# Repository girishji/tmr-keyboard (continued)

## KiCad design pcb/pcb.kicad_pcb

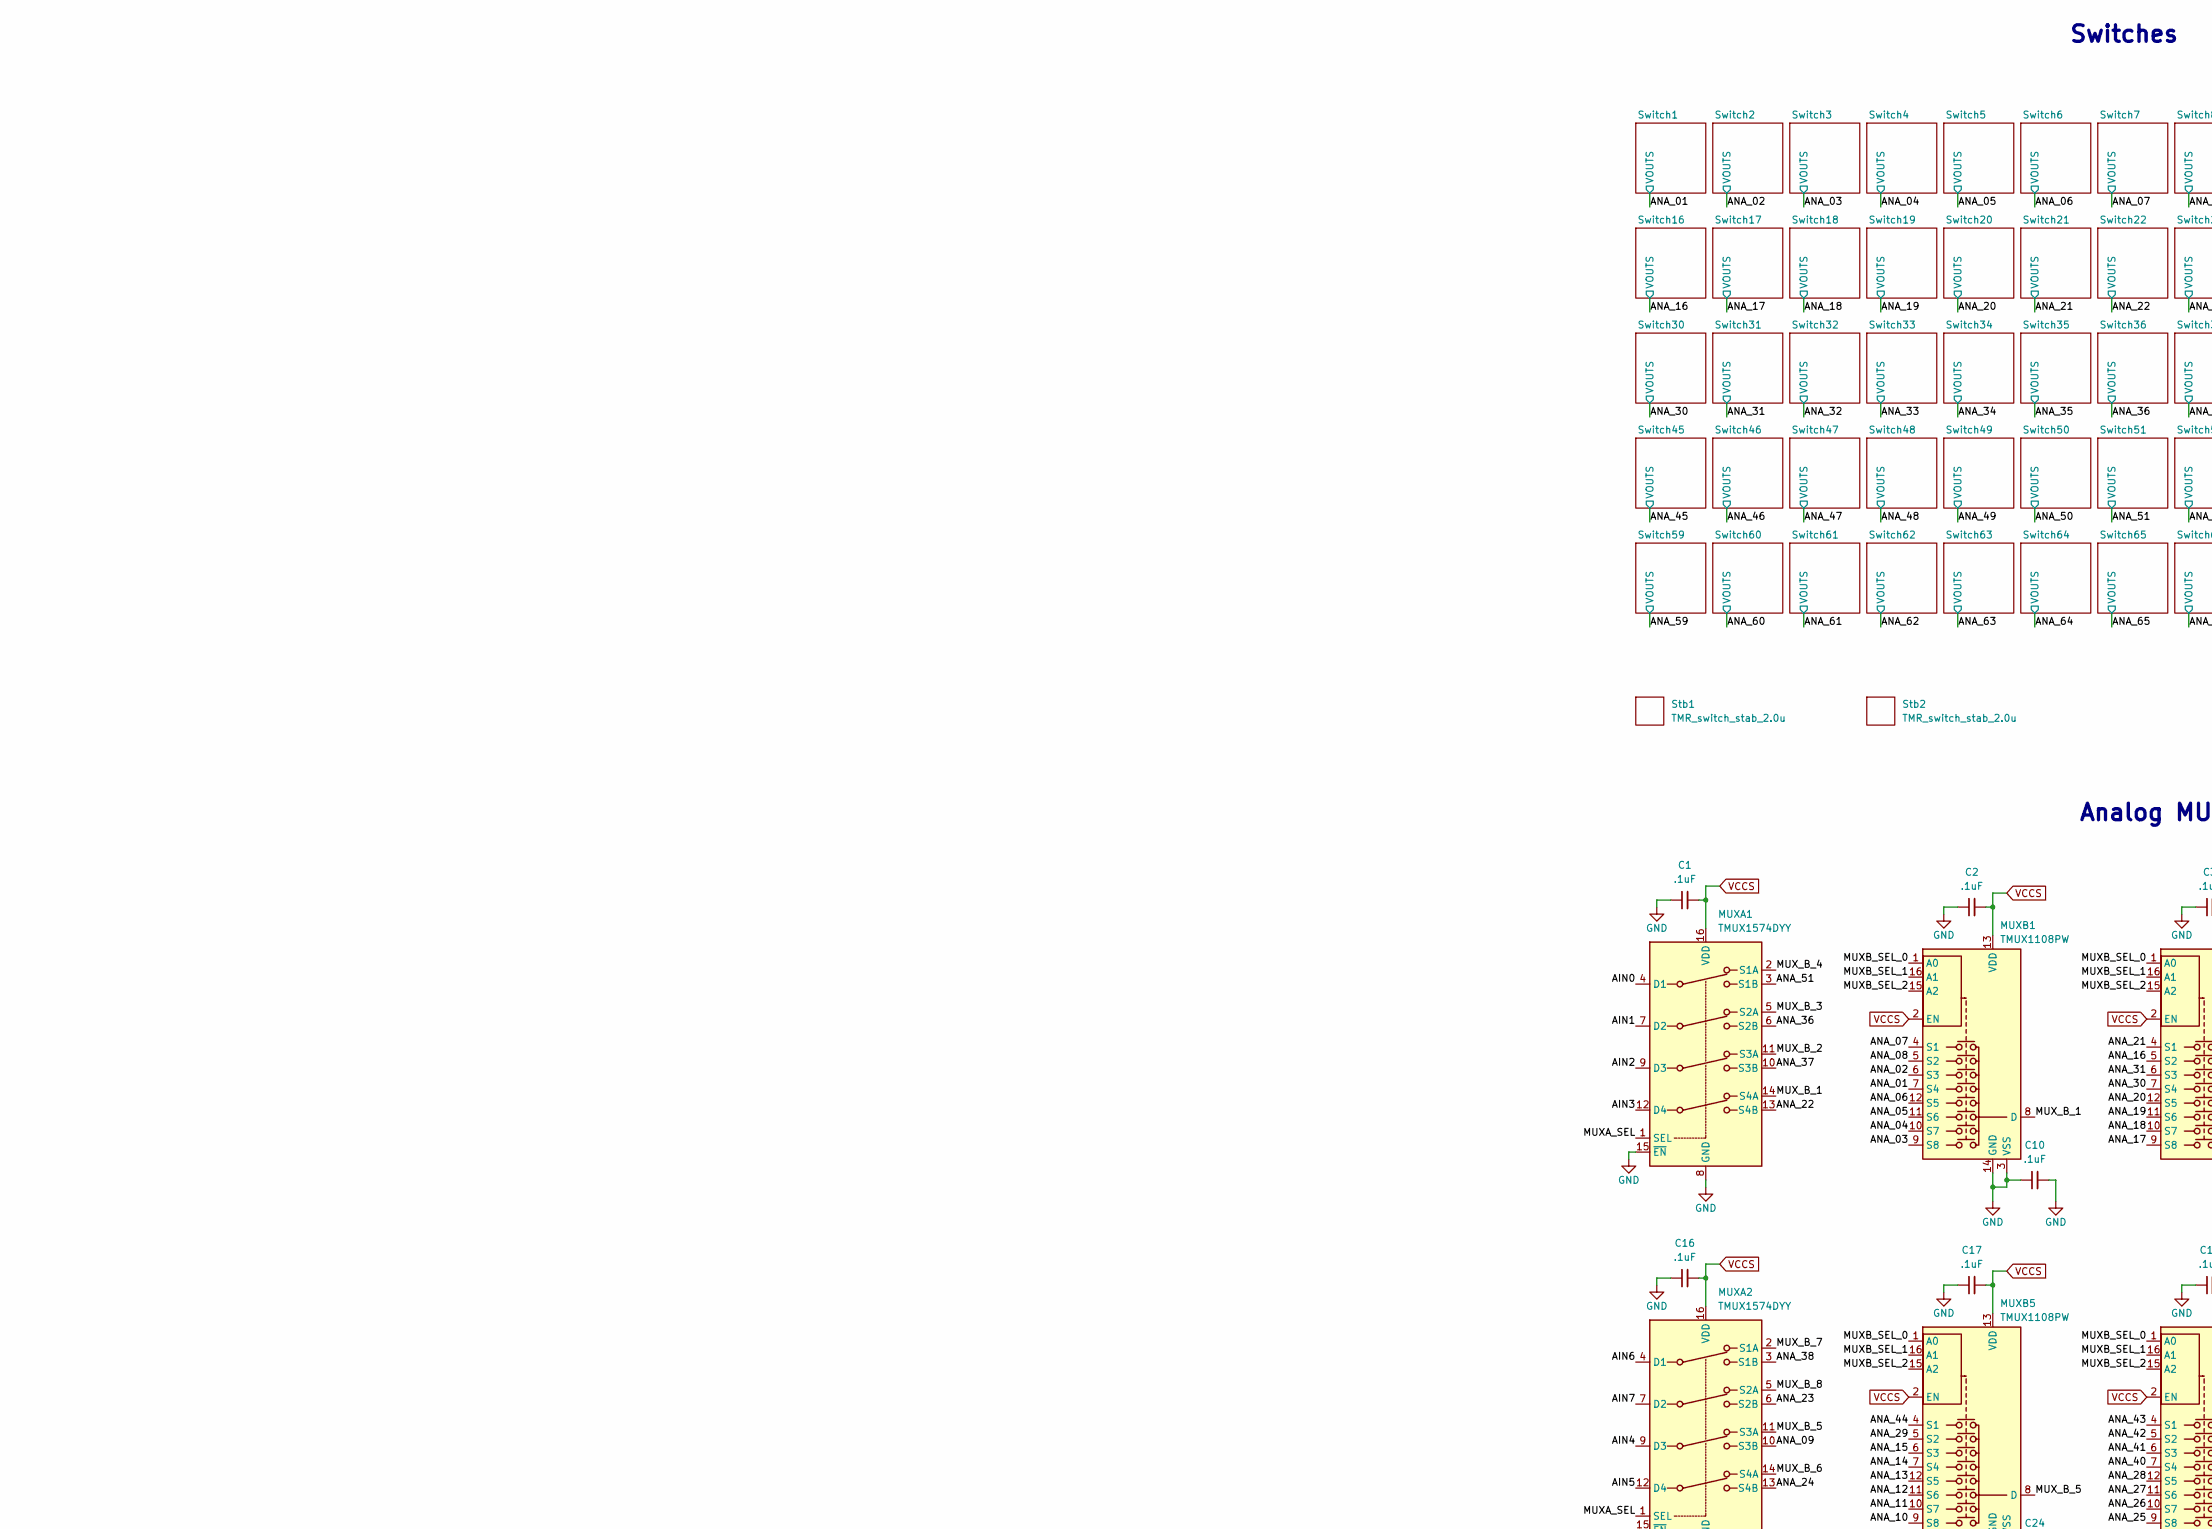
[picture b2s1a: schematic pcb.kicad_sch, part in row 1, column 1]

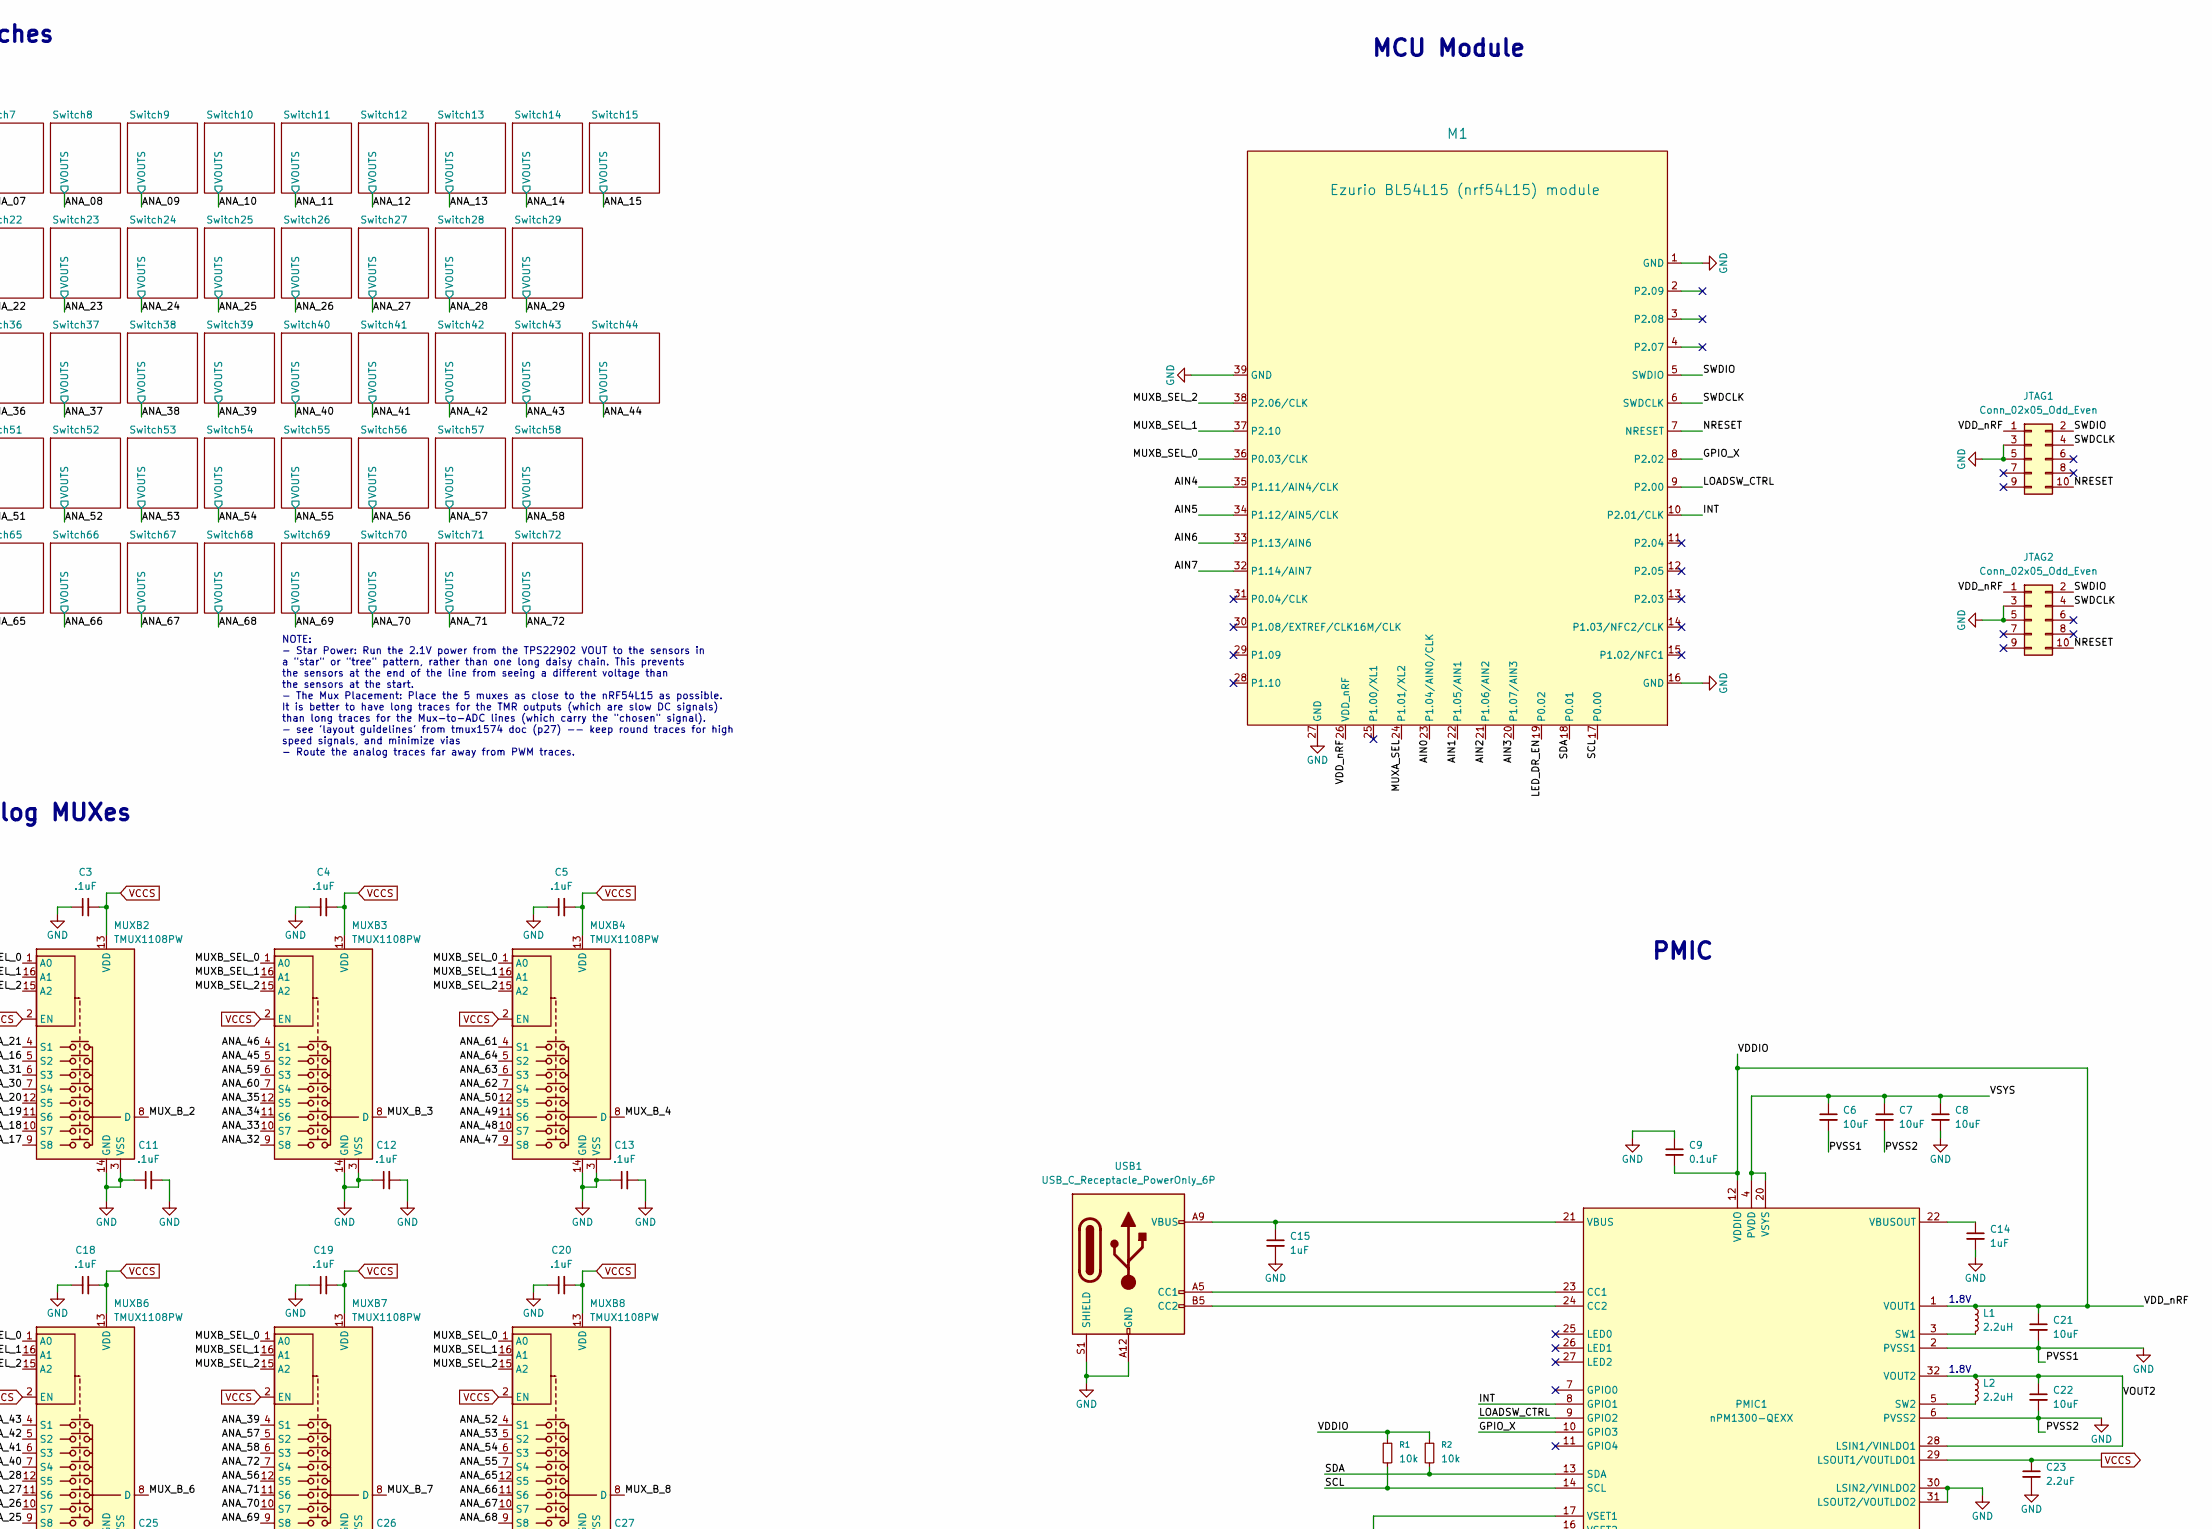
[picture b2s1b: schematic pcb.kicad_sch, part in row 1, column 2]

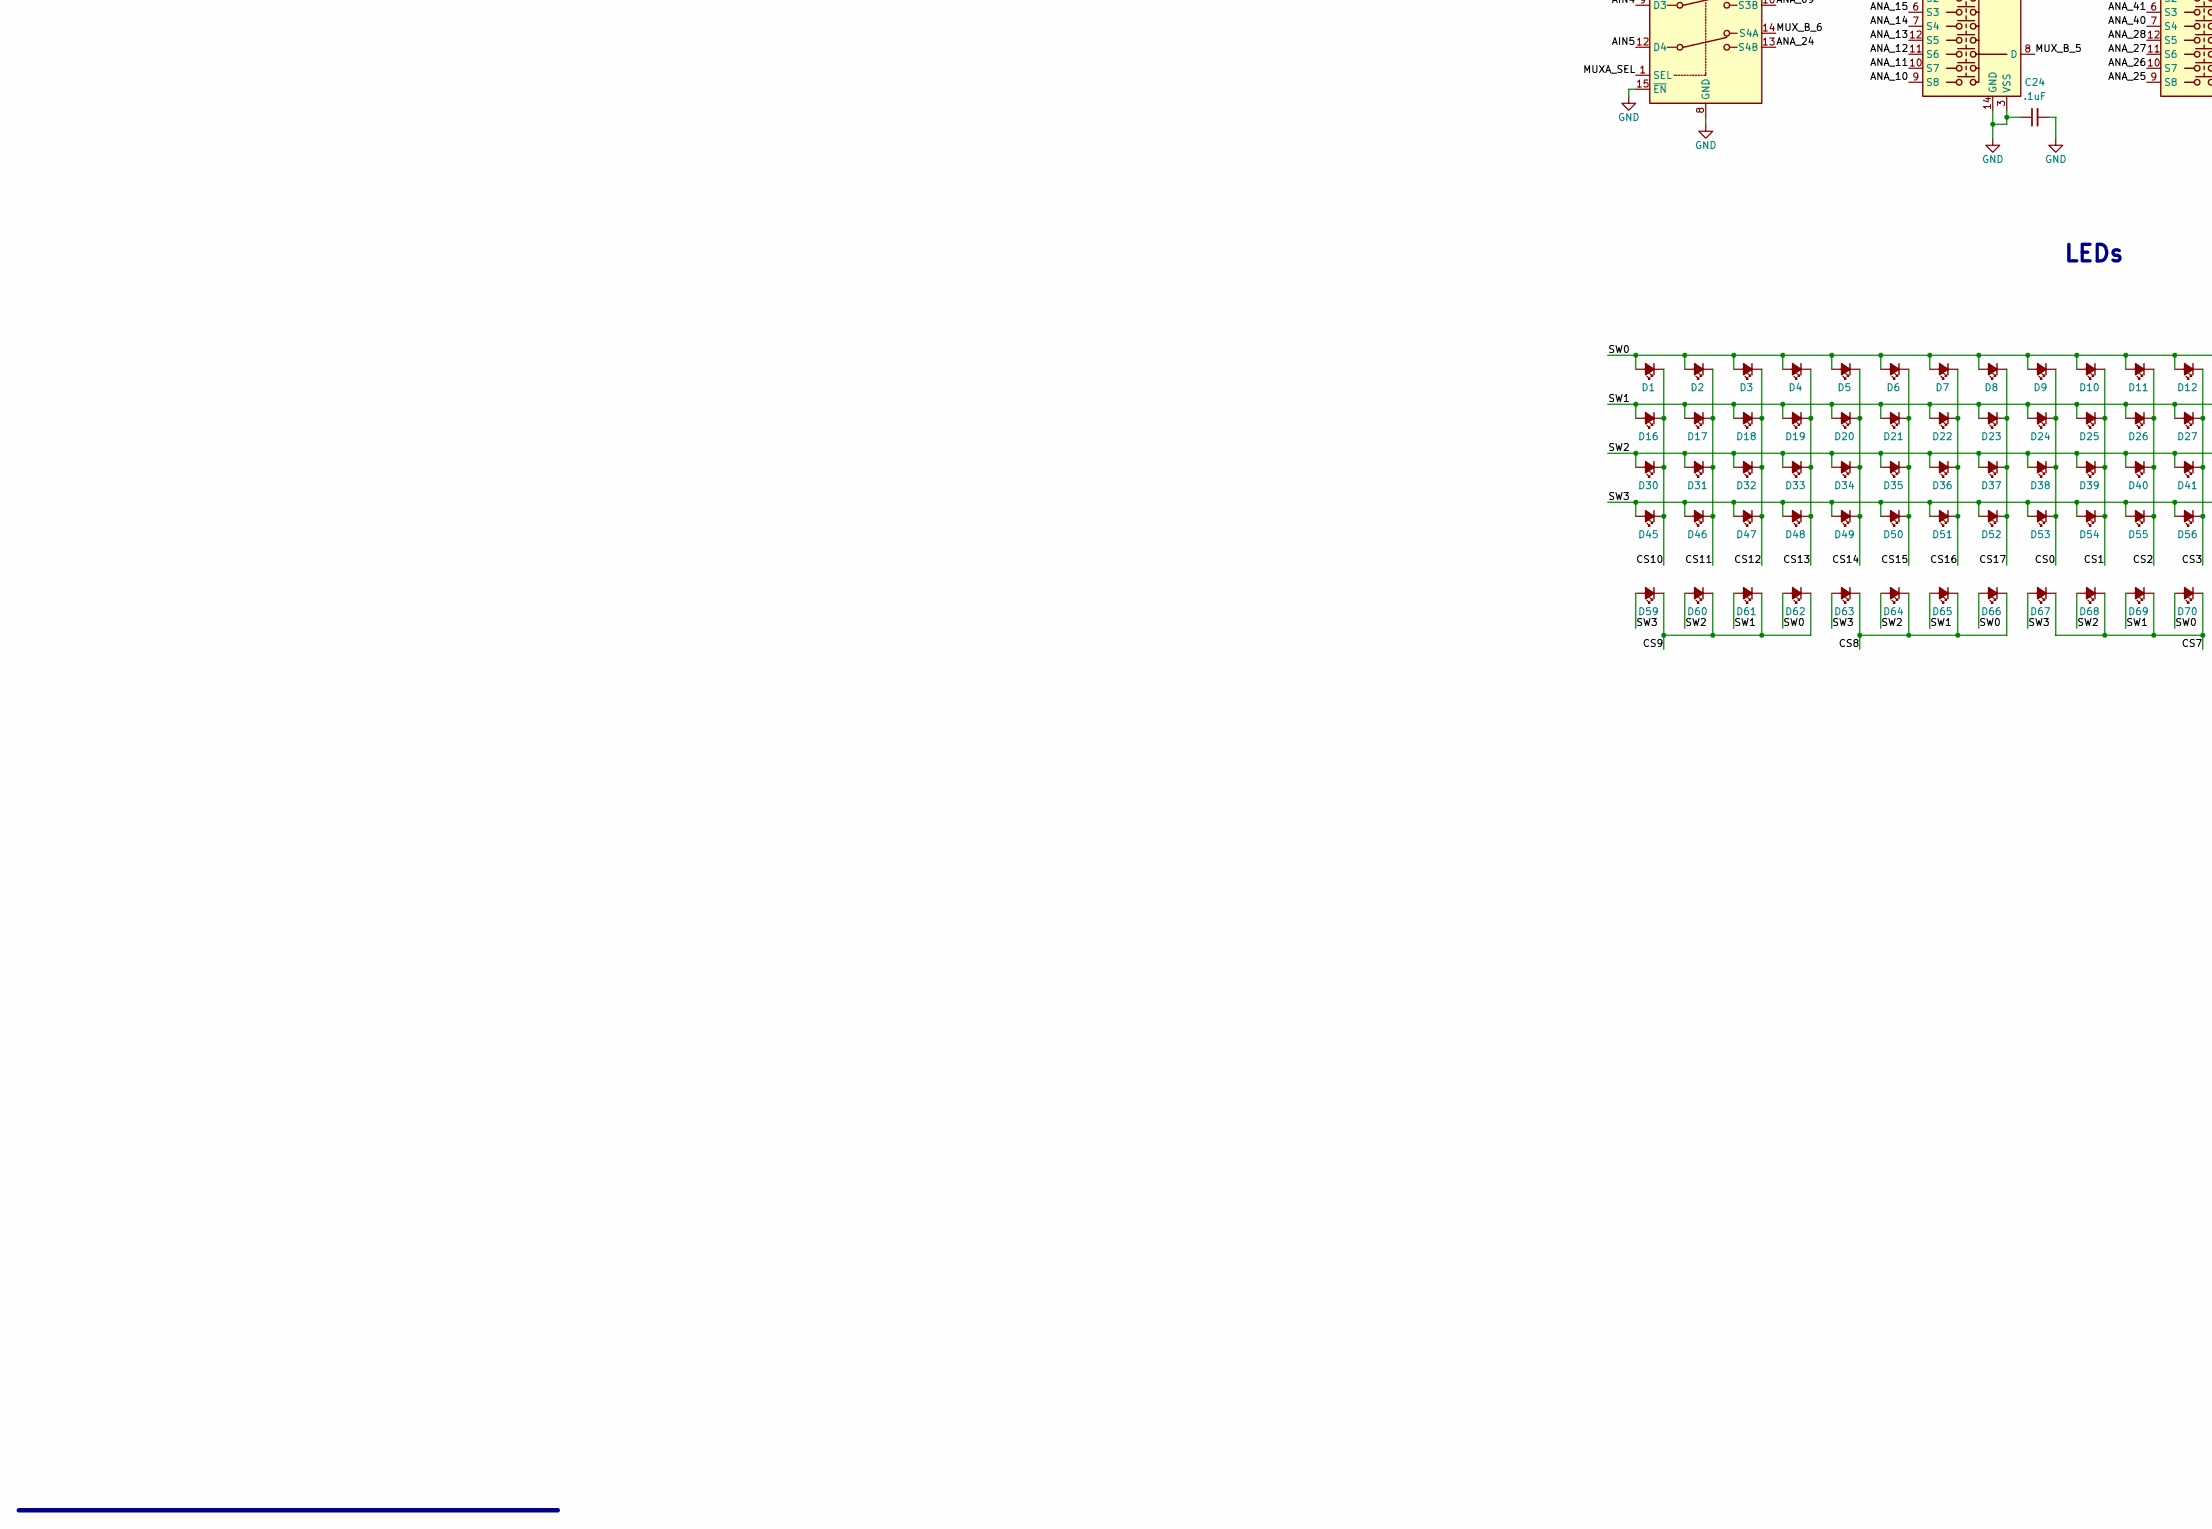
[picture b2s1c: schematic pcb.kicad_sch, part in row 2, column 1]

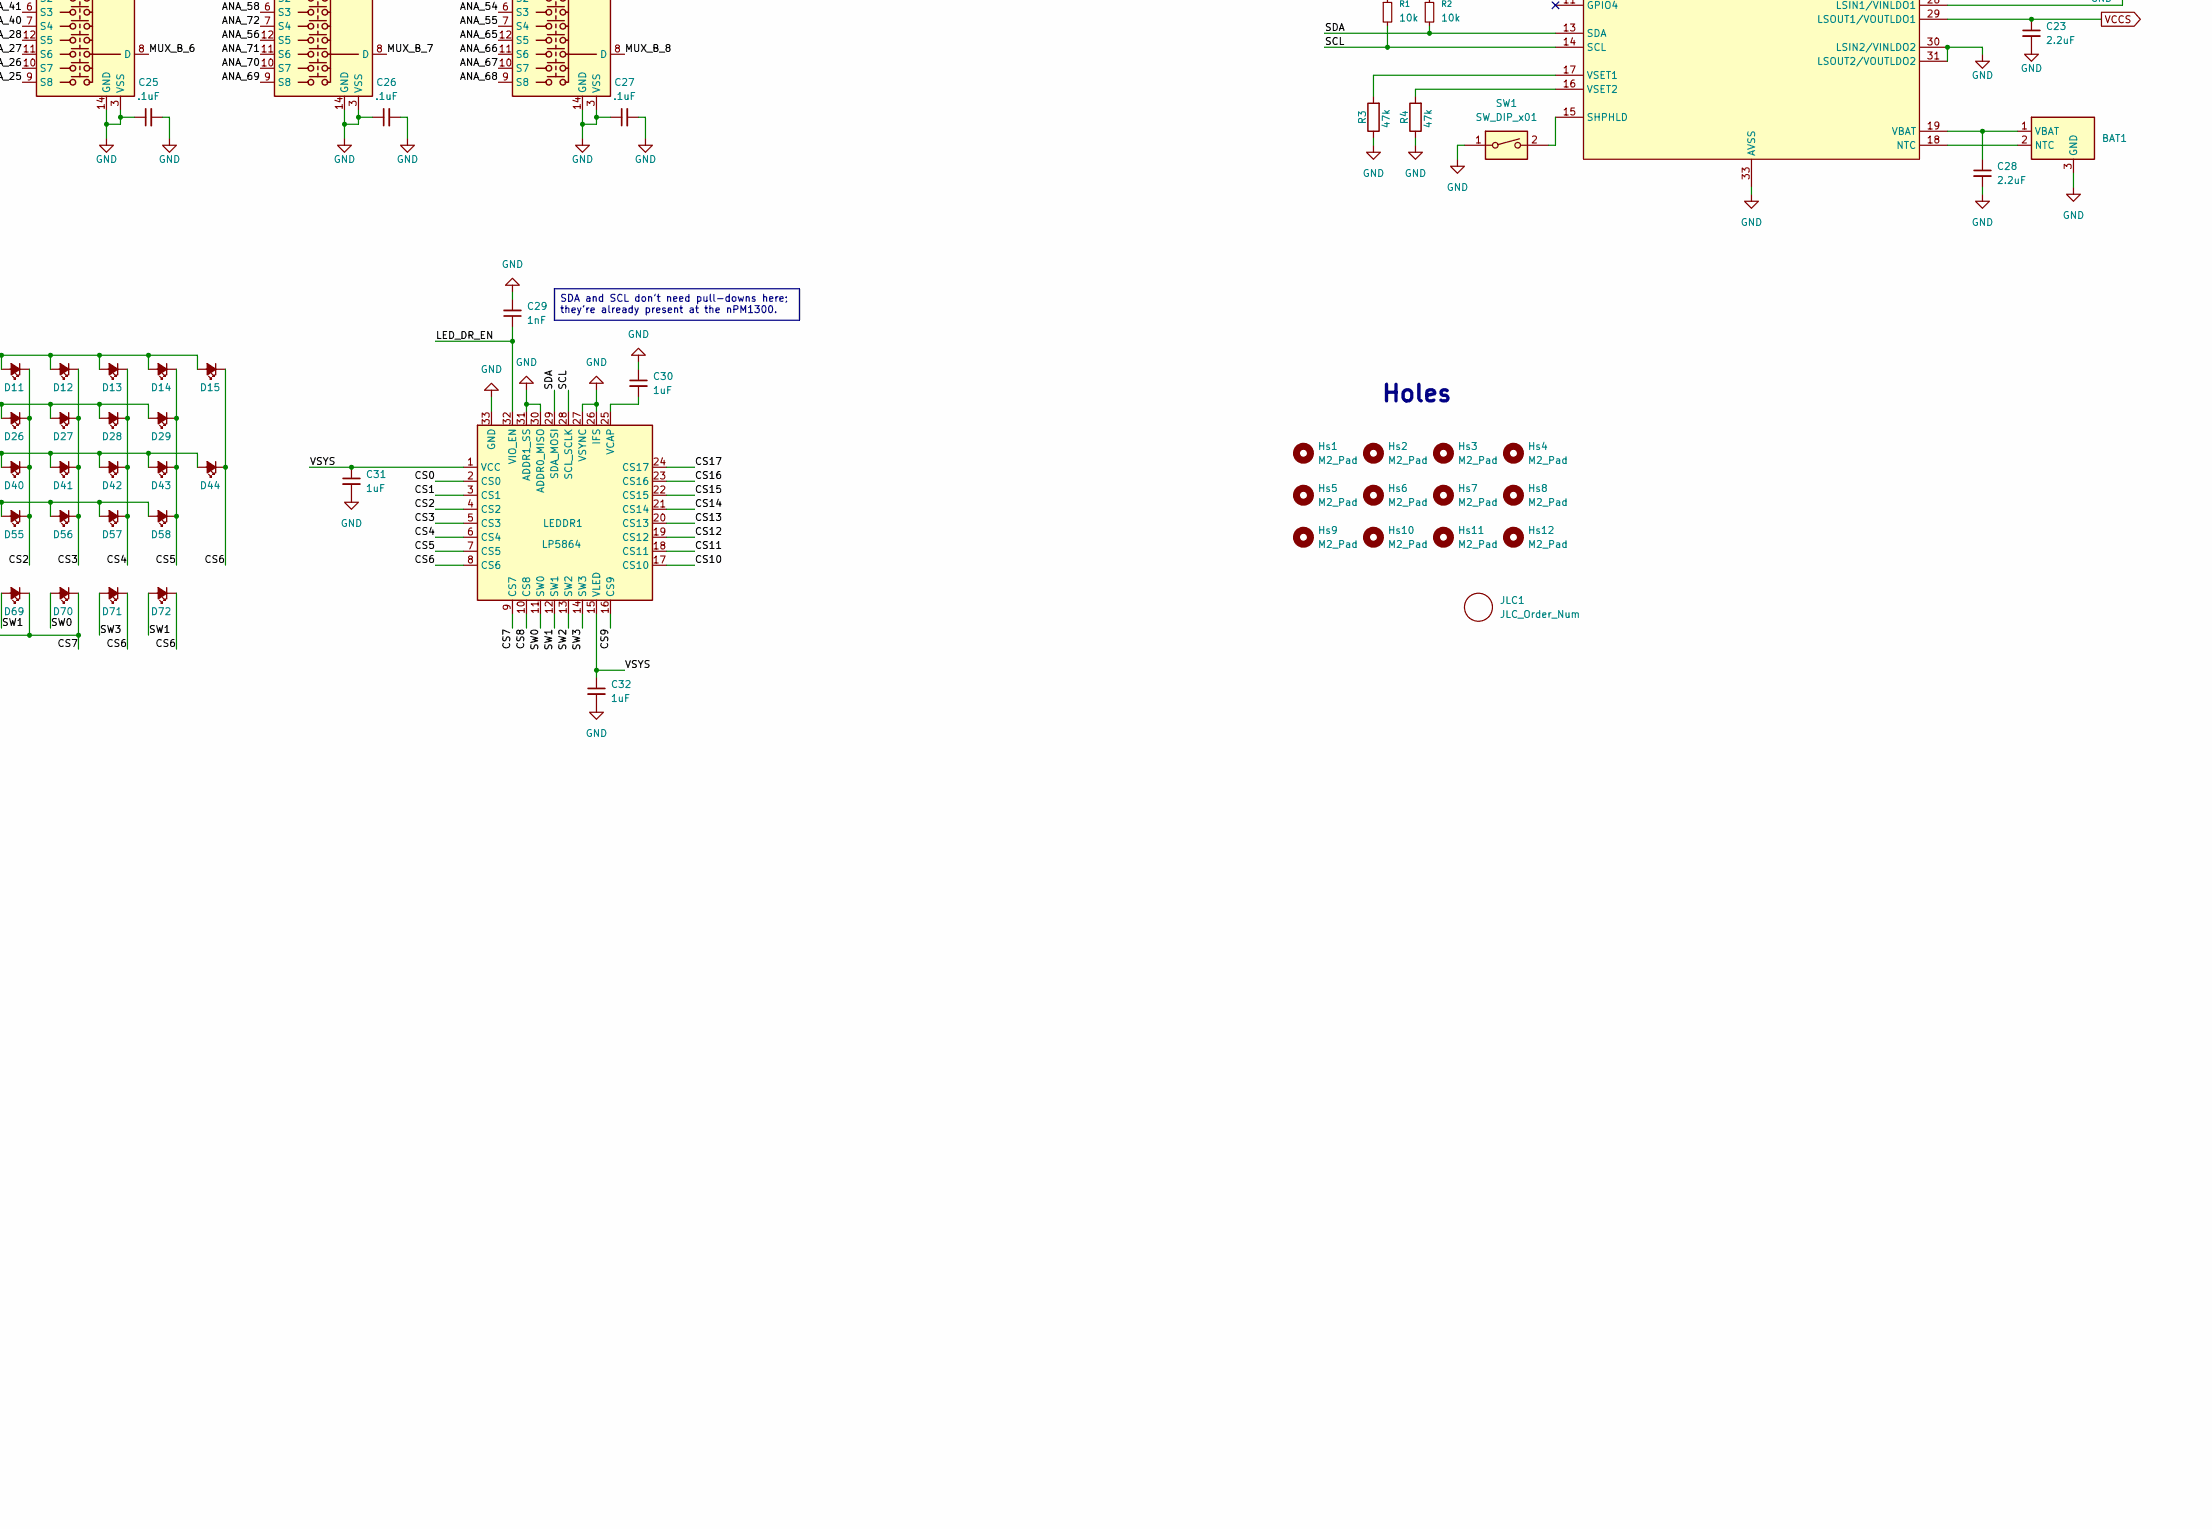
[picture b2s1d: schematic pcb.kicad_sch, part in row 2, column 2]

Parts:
BAT1: JST_SH_SM03B-SRSS-TB_1x03-1MP_P1.00mm_Horizontal
C1, C2, C3, C4, C5, C10, C11, C12, C13, C16, C17, C18, C19, C20, C24, C25, C26, C27: .1uF; C_0402_1005Metric
C6, C7, C8, C21, C22: 10uF; C_0603_1608Metric
C9: 0.1uF; C_0402_1005Metric
C14, C15, C30, C31, C32: 1uF; C_0603_1608Metric
C23, C28: 2.2uF; C_0603_1608Metric
C29: 1nF; C_0603_1608Metric
D1, D2, D3, D4, D5, D6, D7, D8, D9, D10, D11, D12, D13, D14, D15, D16, D17, D18, D19, D20, D21, D22, D23, D24, D25, D26, D27, D28, D29, D30, D31, D32, D33, D34, D35, D36, D37, D38, D39, D40, D41, D42, D43, D44, D45, D46, D47, D48, D49, D50, D51, D52, D53, D54, D55, D56, D57, D58, D59, D60, D61, D62, D63, D64, D65, D66, D67, D68, D69, D70, D71, D72: Green LED; LED_1206_3216Metric_ReverseMount_Hole2.1mm
Hs1, Hs2, Hs3, Hs4, Hs5, Hs6, Hs7, Hs8, Hs9, Hs10, Hs11, Hs12: M2_Pad; MountingHole_2.2mm_M2_ISO7380_Pad_TopBottom
JLC1: JLC_Order_Num
JTAG1: Conn_02x05_Odd_Even; SAMTEC-CLP-105-02-X-D-A
JTAG2: Conn_02x05_Odd_Even; Tag-Connect_TC2050-IDC-NL_2x05_P1.27mm_Vertical
L1, L2: 2.2uH; L_Samsung_CIGT201610EH2R2MNE
LEDDR1: LP5864; VQFN-32-1EP_4x4mm_P0.4mm_EP2.8x2.8mm_ThermalVias
M1: Ezurio BL54L15 (nrf54L15) module; Ezurio_BL54L15_Module
MUXA1, MUXA2: TMUX1574DYY; Texas_DYY0016A_TSOT-23-16_2x4.2mm_P0.5mm
MUXB1, MUXB2, MUXB3, MUXB4, MUXB5, MUXB6, MUXB7, MUXB8: TMUX1108PW; TSSOP-16_4.4x5mm_P0.65mm
PMIC1: nPM1300-QEXX; QFN-32-1EP_5x5mm_P0.5mm_EP3.6x3.6mm_ThermalVias
R1, R2: 10k; R_0402_1005Metric
R3, R4: 47k; R_0402_1005Metric
SW1: SW_DIP_x01; Button_Switch_3x4x2.5
Stb1, Stb2: TMR_switch_stab_2.0u; Stabilizer_Lowpro_2U
USB1: USB_C_Receptacle_PowerOnly_6P; USB_C_Receptacle_GCT_USB4125-xx-x-0190_6P_TopMnt_Horizontal

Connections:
/AIN0: M1.23 (P1.04/AIN0/CLK), MUXA1.4 (D1)
/AIN1: M1.22 (P1.05/AIN1), MUXA1.7 (D2)
/AIN2: M1.21 (P1.06/AIN2), MUXA1.9 (D3)
/AIN3: M1.20 (P1.07/AIN3), MUXA1.12 (D4)
/AIN4: M1.35 (P1.11/AIN4/CLK), MUXA2.9 (D3)
/AIN5: M1.34 (P1.12/AIN5/CLK), MUXA2.12 (D4)
/AIN6: M1.33 (P1.13/AIN6), MUXA2.4 (D1)
/AIN7: M1.32 (P1.14/AIN7), MUXA2.7 (D2)
/ANA_01: MUXB1.7 (S4); also elsewhere on the board
/ANA_02: MUXB1.6 (S3); also elsewhere on the board
/ANA_03: MUXB1.9 (S8); also elsewhere on the board
/ANA_04: MUXB1.10 (S7); also elsewhere on the board
/ANA_05: MUXB1.11 (S6); also elsewhere on the board
/ANA_06: MUXB1.12 (S5); also elsewhere on the board
/ANA_07: MUXB1.4 (S1); also elsewhere on the board
/ANA_08: MUXB1.5 (S2); also elsewhere on the board
/ANA_09: MUXA2.10 (S3B); also elsewhere on the board
/ANA_10: MUXB5.9 (S8); also elsewhere on the board
/ANA_11: MUXB5.10 (S7); also elsewhere on the board
/ANA_12: MUXB5.11 (S6); also elsewhere on the board
/ANA_13: MUXB5.12 (S5); also elsewhere on the board
/ANA_14: MUXB5.7 (S4); also elsewhere on the board
/ANA_15: MUXB5.6 (S3); also elsewhere on the board
/ANA_16: MUXB2.5 (S2); also elsewhere on the board
/ANA_17: MUXB2.9 (S8); also elsewhere on the board
/ANA_18: MUXB2.10 (S7); also elsewhere on the board
/ANA_19: MUXB2.11 (S6); also elsewhere on the board
/ANA_20: MUXB2.12 (S5); also elsewhere on the board
/ANA_21: MUXB2.4 (S1); also elsewhere on the board
/ANA_22: MUXA1.13 (S4B); also elsewhere on the board
/ANA_23: MUXA2.6 (S2B); also elsewhere on the board
/ANA_24: MUXA2.13 (S4B); also elsewhere on the board
/ANA_25: MUXB6.9 (S8); also elsewhere on the board
/ANA_26: MUXB6.10 (S7); also elsewhere on the board
/ANA_27: MUXB6.11 (S6); also elsewhere on the board
/ANA_28: MUXB6.12 (S5); also elsewhere on the board
/ANA_29: MUXB5.5 (S2); also elsewhere on the board
/ANA_30: MUXB2.7 (S4); also elsewhere on the board
/ANA_31: MUXB2.6 (S3); also elsewhere on the board
/ANA_32: MUXB3.9 (S8); also elsewhere on the board
/ANA_33: MUXB3.10 (S7); also elsewhere on the board
/ANA_34: MUXB3.11 (S6); also elsewhere on the board
/ANA_35: MUXB3.12 (S5); also elsewhere on the board
/ANA_36: MUXA1.6 (S2B); also elsewhere on the board
/ANA_37: MUXA1.10 (S3B); also elsewhere on the board
/ANA_38: MUXA2.3 (S1B); also elsewhere on the board
/ANA_39: MUXB7.4 (S1); also elsewhere on the board
/ANA_40: MUXB6.7 (S4); also elsewhere on the board
/ANA_41: MUXB6.6 (S3); also elsewhere on the board
/ANA_42: MUXB6.5 (S2); also elsewhere on the board
/ANA_43: MUXB6.4 (S1); also elsewhere on the board
/ANA_44: MUXB5.4 (S1); also elsewhere on the board
/ANA_45: MUXB3.5 (S2); also elsewhere on the board
/ANA_46: MUXB3.4 (S1); also elsewhere on the board
/ANA_47: MUXB4.9 (S8); also elsewhere on the board
/ANA_48: MUXB4.10 (S7); also elsewhere on the board
/ANA_49: MUXB4.11 (S6); also elsewhere on the board
/ANA_50: MUXB4.12 (S5); also elsewhere on the board
/ANA_51: MUXA1.3 (S1B); also elsewhere on the board
/ANA_52: MUXB8.4 (S1); also elsewhere on the board
/ANA_53: MUXB8.5 (S2); also elsewhere on the board
/ANA_54: MUXB8.6 (S3); also elsewhere on the board
/ANA_55: MUXB8.7 (S4); also elsewhere on the board
/ANA_56: MUXB7.12 (S5); also elsewhere on the board
/ANA_57: MUXB7.5 (S2); also elsewhere on the board
/ANA_58: MUXB7.6 (S3); also elsewhere on the board
/ANA_59: MUXB3.6 (S3); also elsewhere on the board
/ANA_60: MUXB3.7 (S4); also elsewhere on the board
/ANA_61: MUXB4.4 (S1); also elsewhere on the board
/ANA_62: MUXB4.7 (S4); also elsewhere on the board
/ANA_63: MUXB4.6 (S3); also elsewhere on the board
/ANA_64: MUXB4.5 (S2); also elsewhere on the board
/ANA_65: MUXB8.12 (S5); also elsewhere on the board
/ANA_66: MUXB8.11 (S6); also elsewhere on the board
/ANA_67: MUXB8.10 (S7); also elsewhere on the board
/ANA_68: MUXB8.9 (S8); also elsewhere on the board
/ANA_69: MUXB7.9 (S8); also elsewhere on the board
/ANA_70: MUXB7.10 (S7); also elsewhere on the board
/ANA_71: MUXB7.11 (S6); also elsewhere on the board
/ANA_72: MUXB7.7 (S4); also elsewhere on the board
/CS0: D9.1 (K), D24.1 (K), D38.1 (K), D53.1 (K), LEDDR1.2 (CS0)
/CS1: D10.1 (K), D25.1 (K), D39.1 (K), D54.1 (K), LEDDR1.3 (CS1)
/CS2: D11.1 (K), D26.1 (K), D40.1 (K), D55.1 (K), LEDDR1.4 (CS2)
/CS3: D12.1 (K), D27.1 (K), D41.1 (K), D56.1 (K), LEDDR1.5 (CS3)
/CS4: D13.1 (K), D28.1 (K), D42.1 (K), D57.1 (K), LEDDR1.6 (CS4)
/CS5: D14.1 (K), D29.1 (K), D43.1 (K), D58.1 (K), LEDDR1.7 (CS5)
/CS6: D15.1 (K), D44.1 (K), D71.1 (K), D72.1 (K), LEDDR1.8 (CS6)
/CS7: D67.1 (K), D68.1 (K), D69.1 (K), D70.1 (K), LEDDR1.9 (CS7)
/CS8: D63.1 (K), D64.1 (K), D65.1 (K), D66.1 (K), LEDDR1.10 (CS8)
/CS9: D59.1 (K), D60.1 (K), D61.1 (K), D62.1 (K), LEDDR1.16 (CS9)
/CS10: D1.1 (K), D16.1 (K), D30.1 (K), D45.1 (K), LEDDR1.17 (CS10)
/CS11: D2.1 (K), D17.1 (K), D31.1 (K), D46.1 (K), LEDDR1.18 (CS11)
/CS12: D3.1 (K), D18.1 (K), D32.1 (K), D47.1 (K), LEDDR1.19 (CS12)
/CS13: D4.1 (K), D19.1 (K), D33.1 (K), D48.1 (K), LEDDR1.20 (CS13)
/CS14: D5.1 (K), D20.1 (K), D34.1 (K), D49.1 (K), LEDDR1.21 (CS14)
/CS15: D6.1 (K), D21.1 (K), D35.1 (K), D50.1 (K), LEDDR1.22 (CS15)
/CS16: D7.1 (K), D22.1 (K), D36.1 (K), D51.1 (K), LEDDR1.23 (CS16)
/CS17: D8.1 (K), D23.1 (K), D37.1 (K), D52.1 (K), LEDDR1.24 (CS17)
/GPIO_X: M1.8 (P2.02), PMIC1.10 (GPIO3)
/INT: M1.10 (P2.01/CLK), PMIC1.8 (GPIO1)
/LED_DR_EN: C29.1, LEDDR1.32 (VIO_EN), M1.19 (P0.02)
/LOADSW_CTRL: M1.9 (P2.00), PMIC1.9 (GPIO2)
/MUXA_SEL: M1.24 (P1.01/XL2), MUXA1.1 (SEL), MUXA2.1 (SEL)
/MUXB_SEL_0: M1.36 (P0.03/CLK), MUXB1.1 (A0), MUXB2.1 (A0), MUXB3.1 (A0), MUXB4.1 (A0), MUXB5.1 (A0), MUXB6.1 (A0), MUXB7.1 (A0), MUXB8.1 (A0)
/MUXB_SEL_1: M1.37 (P2.10), MUXB1.16 (A1), MUXB2.16 (A1), MUXB3.16 (A1), MUXB4.16 (A1), MUXB5.16 (A1), MUXB6.16 (A1), MUXB7.16 (A1), MUXB8.16 (A1)
/MUXB_SEL_2: M1.38 (P2.06/CLK), MUXB1.15 (A2), MUXB2.15 (A2), MUXB3.15 (A2), MUXB4.15 (A2), MUXB5.15 (A2), MUXB6.15 (A2), MUXB7.15 (A2), MUXB8.15 (A2)
/MUX_B_1: MUXA1.14 (S4A), MUXB1.8 (D)
/MUX_B_2: MUXA1.11 (S3A), MUXB2.8 (D)
/MUX_B_3: MUXA1.5 (S2A), MUXB3.8 (D)
/MUX_B_4: MUXA1.2 (S1A), MUXB4.8 (D)
/MUX_B_5: MUXA2.11 (S3A), MUXB5.8 (D)
/MUX_B_6: MUXA2.14 (S4A), MUXB6.8 (D)
/MUX_B_7: MUXA2.2 (S1A), MUXB7.8 (D)
/MUX_B_8: MUXA2.5 (S2A), MUXB8.8 (D)
/NRESET: JTAG1.10, JTAG2.10, M1.7 (NRESET)
/SCL: LEDDR1.28 (SCL_SCLK), M1.17 (P0.00), PMIC1.14 (SCL), R1.2
/SDA: LEDDR1.29 (SDA_MOSI), M1.18 (P0.01), PMIC1.13 (SDA), R2.2
/SW0: D1.2 (A), D2.2 (A), D3.2 (A), D4.2 (A), D5.2 (A), D6.2 (A), D7.2 (A), D8.2 (A), D9.2 (A), D10.2 (A), D11.2 (A), D12.2 (A), D13.2 (A), D14.2 (A), D15.2 (A), D62.2 (A), D66.2 (A), D70.2 (A), LEDDR1.11 (SW0)
/SW1: D16.2 (A), D17.2 (A), D18.2 (A), D19.2 (A), D20.2 (A), D21.2 (A), D22.2 (A), D23.2 (A), D24.2 (A), D25.2 (A), D26.2 (A), D27.2 (A), D28.2 (A), D29.2 (A), D61.2 (A), D65.2 (A), D69.2 (A), D72.2 (A), LEDDR1.12 (SW1)
/SW2: D30.2 (A), D31.2 (A), D32.2 (A), D33.2 (A), D34.2 (A), D35.2 (A), D36.2 (A), D37.2 (A), D38.2 (A), D39.2 (A), D40.2 (A), D41.2 (A), D42.2 (A), D43.2 (A), D44.2 (A), D60.2 (A), D64.2 (A), D68.2 (A), LEDDR1.13 (SW2)
/SW3: D45.2 (A), D46.2 (A), D47.2 (A), D48.2 (A), D49.2 (A), D50.2 (A), D51.2 (A), D52.2 (A), D53.2 (A), D54.2 (A), D55.2 (A), D56.2 (A), D57.2 (A), D58.2 (A), D59.2 (A), D63.2 (A), D67.2 (A), D71.2 (A), LEDDR1.14 (SW3)
/SWDCLK: JTAG1.4, JTAG2.4, M1.6 (SWDCLK)
/SWDIO: JTAG1.2, JTAG2.2, M1.5 (SWDIO)
/VDDIO: C9.2, C21.1, JTAG1.1, JTAG2.1, L1.1, M1.26 (VDD_nRF), PMIC1.1 (VOUT1), PMIC1.12 (VDDIO), R1.1, R2.1
/VOUT2: C22.1, L2.1, PMIC1.28 (LSIN1/VINLDO1), PMIC1.32 (VOUT2)
/VSYS: C6.1, C7.1, C8.1, C31.1, C32.1, LEDDR1.1 (VCC), LEDDR1.15 (VLED), PMIC1.4 (PVDD), PMIC1.20 (VSYS)
GND: BAT1.3 (GND), C1.1, C2.1, C3.1, C4.1, C5.1, C6.2, C7.2, C8.2, C9.1, C10.1, C10.2, C11.1, C11.2, C12.1, C12.2, C13.1, C13.2, C14.2, C15.2, C16.1, C17.1, C18.1, C19.1, C20.1, C21.2, C22.2, C23.2, C24.1, C24.2, C25.1, C25.2, C26.1, C26.2, C27.1, C27.2, C28.2, C29.2, C30.1, C31.2, C32.2, JTAG1.3, JTAG1.5, JTAG2.3, JTAG2.5, LEDDR1.26 (IFS), LEDDR1.27 (VSYNC), LEDDR1.30 (ADDR0_MISO), LEDDR1.31 (ADDR1_SS), LEDDR1.33 (GND), M1.1 (GND), M1.16 (GND), M1.27 (GND), M1.39 (GND), MUXA1.8 (GND), MUXA1.15 (~EN), MUXA2.8 (GND), MUXA2.15 (~EN), MUXB1.3 (VSS), MUXB1.14 (GND), MUXB2.3 (VSS), MUXB2.14 (GND), MUXB3.3 (VSS), MUXB3.14 (GND), MUXB4.3 (VSS), MUXB4.14 (GND), MUXB5.3 (VSS), MUXB5.14 (GND), MUXB6.3 (VSS), MUXB6.14 (GND), MUXB7.3 (VSS), MUXB7.14 (GND), MUXB8.3 (VSS), MUXB8.14 (GND), PMIC1.2 (PVSS1), PMIC1.6 (PVSS2), PMIC1.30 (LSIN2/VINLDO2), PMIC1.31 (LSOUT2/VOUTLDO2), PMIC1.33 (AVSS), R3.1, R4.1, SW1.1, USB1.A12 (GND), USB1.B12 (GND), USB1.S1 (SHIELD); also elsewhere on the board
unnamed: BAT1.2 (NTC), PMIC1.18 (NTC)
unnamed: BAT1.1 (VBAT), C28.1, PMIC1.19 (VBAT)
unnamed: C30.2, LEDDR1.25 (VCAP)
unnamed: PMIC1.23 (CC1), USB1.A5 (CC1)
unnamed: PMIC1.24 (CC2), USB1.B5 (CC2)
unnamed: PMIC1.15 (SHPHLD), SW1.2
unnamed: L1.2, PMIC1.3 (SW1)
unnamed: L2.2, PMIC1.5 (SW2)
unnamed: C15.1, PMIC1.21 (VBUS), USB1.A9 (VBUS), USB1.B9 (VBUS)
unnamed: C14.1, PMIC1.22 (VBUSOUT)
unnamed: PMIC1.17 (VSET1), R3.2
unnamed: PMIC1.16 (VSET2), R4.2
VCCS: C1.2, C2.2, C3.2, C4.2, C5.2, C16.2, C17.2, C18.2, C19.2, C20.2, C23.1, MUXA1.16 (VDD), MUXA2.16 (VDD), MUXB1.2 (EN), MUXB1.13 (VDD), MUXB2.2 (EN), MUXB2.13 (VDD), MUXB3.2 (EN), MUXB3.13 (VDD), MUXB4.2 (EN), MUXB4.13 (VDD), MUXB5.2 (EN), MUXB5.13 (VDD), MUXB6.2 (EN), MUXB6.13 (VDD), MUXB7.2 (EN), MUXB7.13 (VDD), MUXB8.2 (EN), MUXB8.13 (VDD), PMIC1.29 (LSOUT1/VOUTLDO1); also elsewhere on the board

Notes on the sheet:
Holes
1.8V
MCU Module
Analog MUXes
LEDs
PMIC
NOTE: - Star Power: Run the 2.1V power from the TPS22902 VOUT to the sensors in a "star" or "tree" pattern, rather than one long daisy chain. This prevents the sensors at the end of the line from seeing a different voltage than the sensors at the start. - The Mux Placement: Place the 5 muxes as clo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
Switches
SDA and SCL don't need pull-downs here; they're already present at the nPM1300.
